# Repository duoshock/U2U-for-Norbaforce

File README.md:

#USB to USB for Norbaforce

This U2U is based on Hasu USB to USB with the rearranged component layout to fit Norbaforce housing. It's only compatible with Realforce R1 keyboard. However, It's easy to adapt it for Realforce R2 with the KiCad project.

QMK firmware is recommended - Enter DFU mode without having access to the physical rest switch with command keycode enable. (Although, there is a known issue of this port regarding not registering the board after computer reboot.)

Hasu U2U TMK firmware is also compatible.

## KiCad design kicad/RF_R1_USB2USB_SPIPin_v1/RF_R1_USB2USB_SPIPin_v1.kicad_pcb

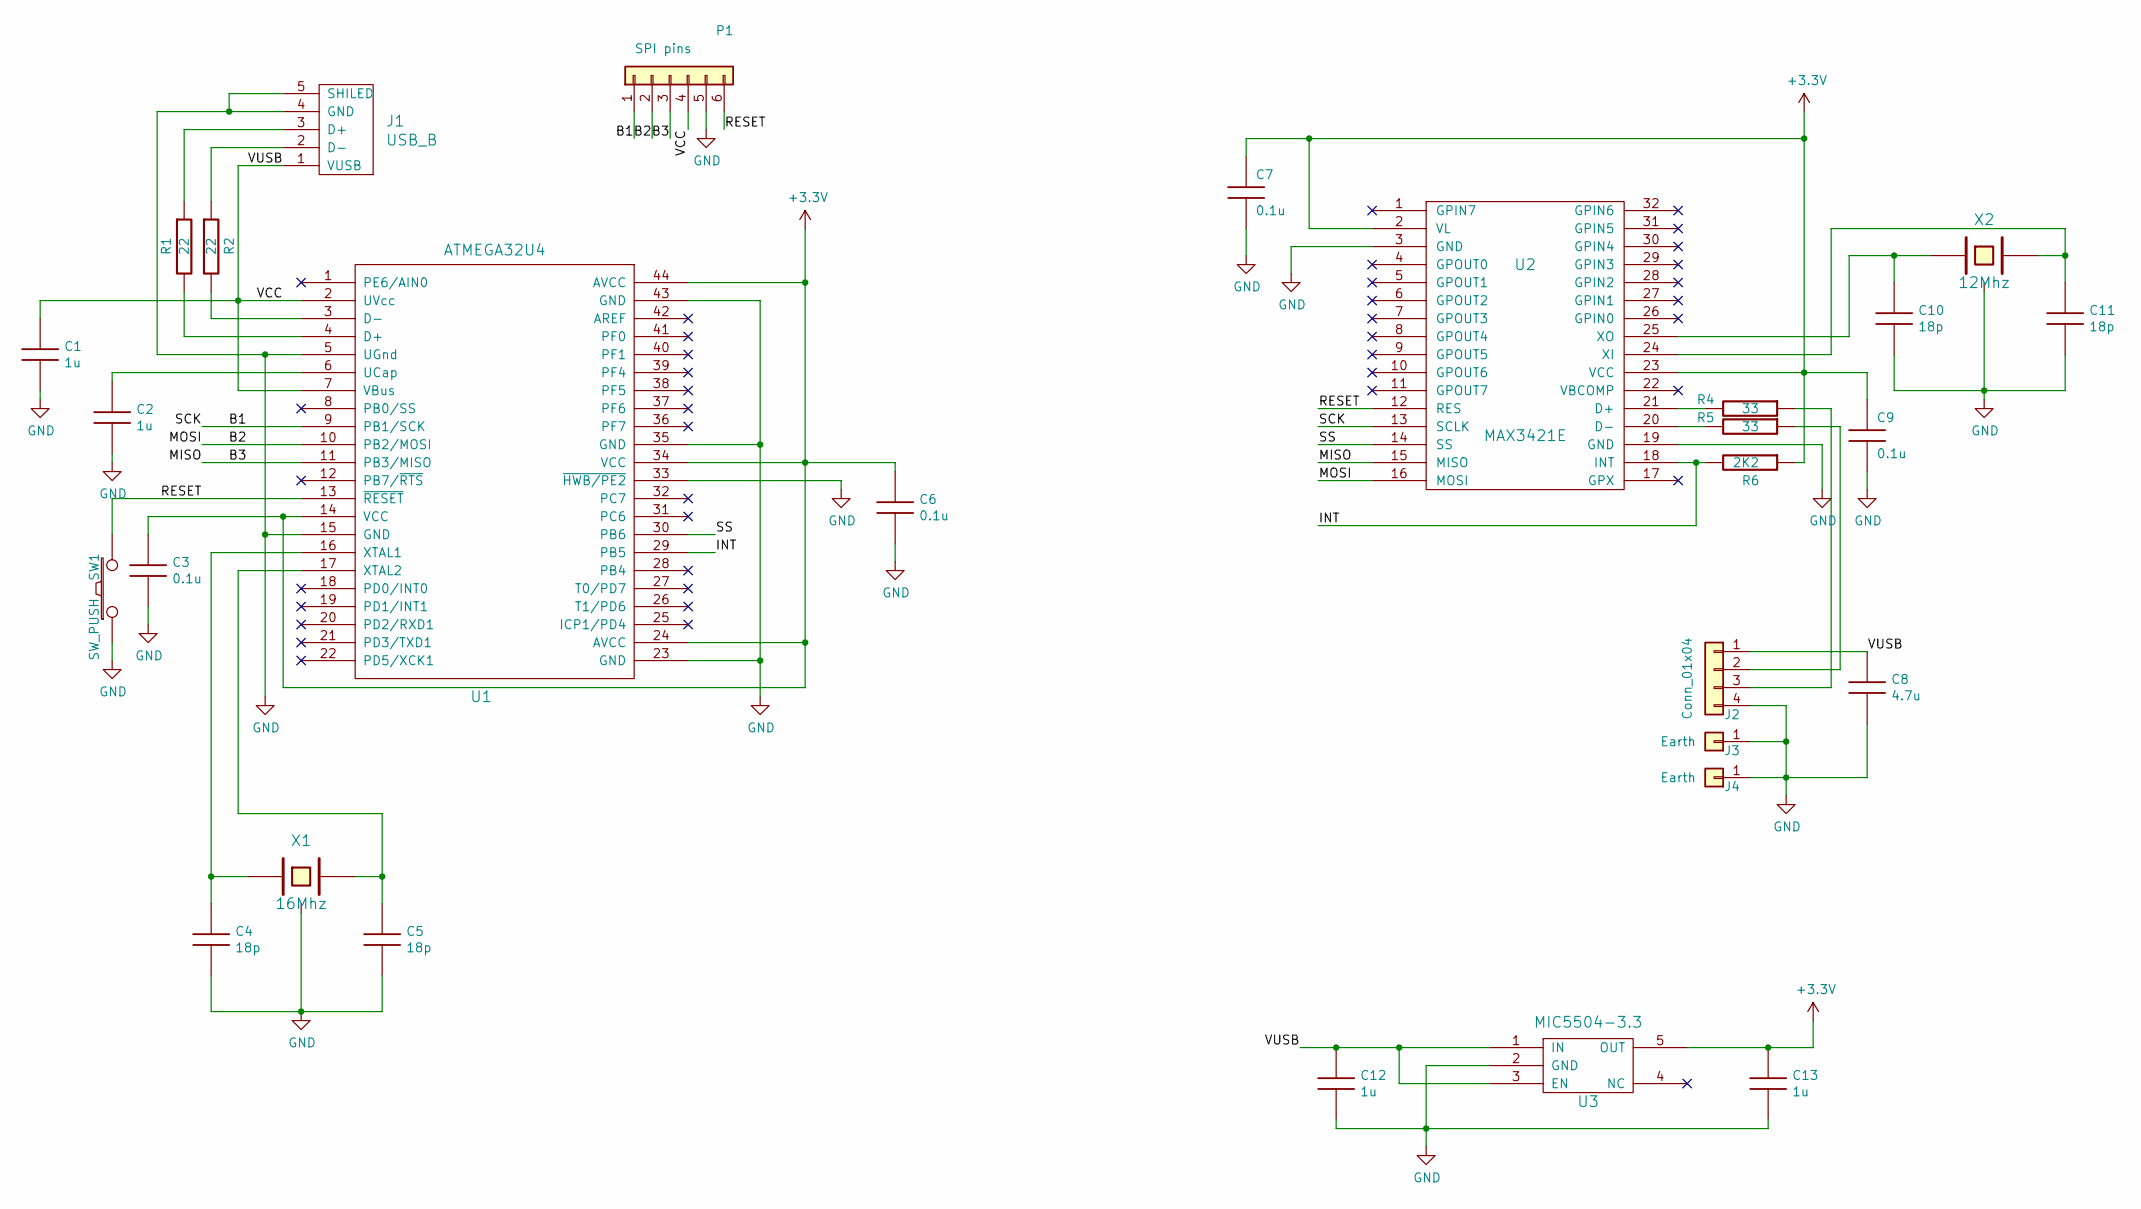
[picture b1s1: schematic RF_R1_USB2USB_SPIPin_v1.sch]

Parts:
C1, C2, C12, C13: 1u; C_0603
C3, C6, C7, C9: 0.1u; C_0603
C4, C5, C10, C11: 18p; C_0603
C8: 4.7u; C_0603
J1: USB_B; USB_Mini-B_Lumberg_2486_01_Horizontal
J2: Conn_01x04; JST_EH_S4B-EH_1x04_P2.50mm_Horizontal
J3, J4: Earth; MountingHole_3mm_Pad_Via
P1: SPI pins; Test Point 1mm x 6
R1, R2: 22; R_0603
R4, R5: 33; R_0603
R6: 2K2; R_0603
SW1: SW_PUSH; SW_SPST_B3U-1000P
U1: ATMEGA32U4; LQFP-44_10x10mm_P0.8mm
U2: MAX3421E; LQFP-32_5x5mm_P0.5mm
U3: MIC5504-3.3; SOT-23-5
X1: 16Mhz; Crystal_FA238-TSX3225
X2: 12Mhz; Crystal_FA238-TSX3225

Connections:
+3V3: C3.1, C6.1, C7.1, C9.1, C13.1, R6.1, U1.14 (VCC), U1.24 (AVCC), U1.34 (VCC), U1.44 (AVCC), U2.2 (VL), U2.23 (VCC), U3.5 (OUT)
/B1: P1.1, U1.9 (PB1/SCK), U2.13 (SCLK)
/B2: P1.2, U1.10 (PB2/MOSI), U2.16 (MOSI)
/B3: P1.3, U1.11 (PB3/MISO), U2.15 (MISO)
/INT: R6.2, U1.29 (PB5), U2.18 (INT)
/RESET: P1.6, SW1.2, U1.13 (~RESET), U2.12 (RES)
/SS: U1.30 (PB6), U2.14 (SS)
/VCC: C1.1, C8.1, C12.1, J1.1 (VUSB), J2.1, P1.4, U1.2 (UVcc), U1.7 (VBus), U3.1 (IN), U3.3 (EN)
GND: C1.2, C2.2, C3.2, C4.2, C5.2, C6.2, C7.2, C8.2, C9.2, C10.2, C11.2, C12.2, C13.2, J1.4 (GND), J1.5 (SHILED), J2.4, J3.1, J4.1, P1.5, SW1.1, U1.5 (UGnd), U1.15 (GND), U1.23 (GND), U1.33 (~HWB/PE2), U1.35 (GND), U1.43 (GND), U2.3 (GND), U2.19 (GND), U3.2 (GND), X1.3, X2.3
unnamed: C2.1, U1.6 (UCap)
unnamed: C4.1, U1.16 (XTAL1), X1.1
unnamed: C5.1, U1.17 (XTAL2), X1.2
unnamed: C10.1, U2.25 (XO), X2.1
unnamed: C11.1, U2.24 (XI), X2.2
unnamed: J1.2 (D-), R2.1
unnamed: J1.3 (D+), R1.1
unnamed: J2.2, R5.1
unnamed: J2.3, R4.1
unnamed: R1.2, U1.4 (D+)
unnamed: R2.2, U1.3 (D-)
unnamed: R4.2, U2.21 (D+)
unnamed: R5.2, U2.20 (D-)

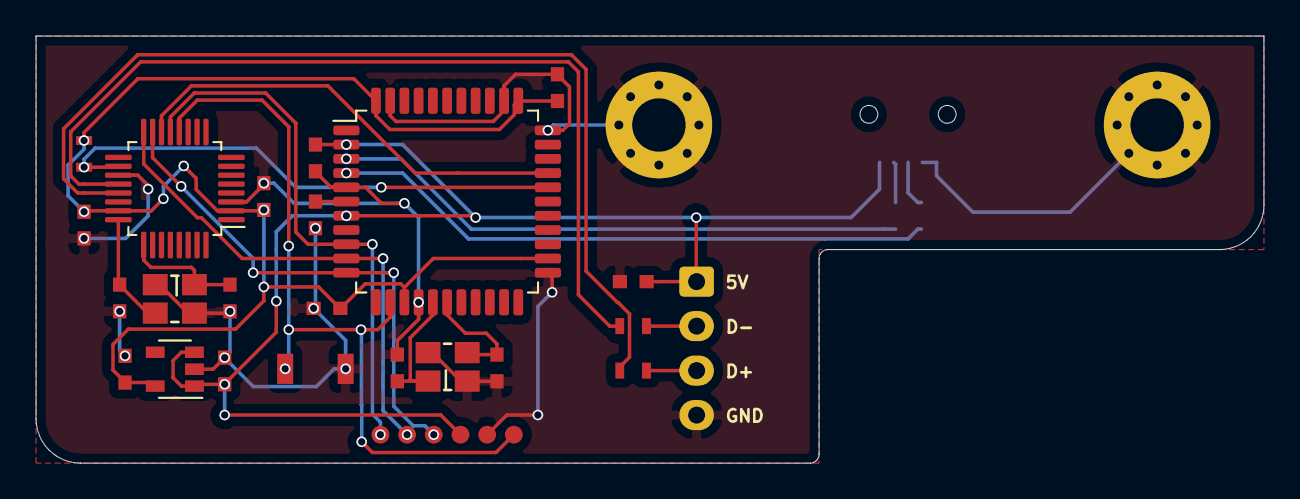
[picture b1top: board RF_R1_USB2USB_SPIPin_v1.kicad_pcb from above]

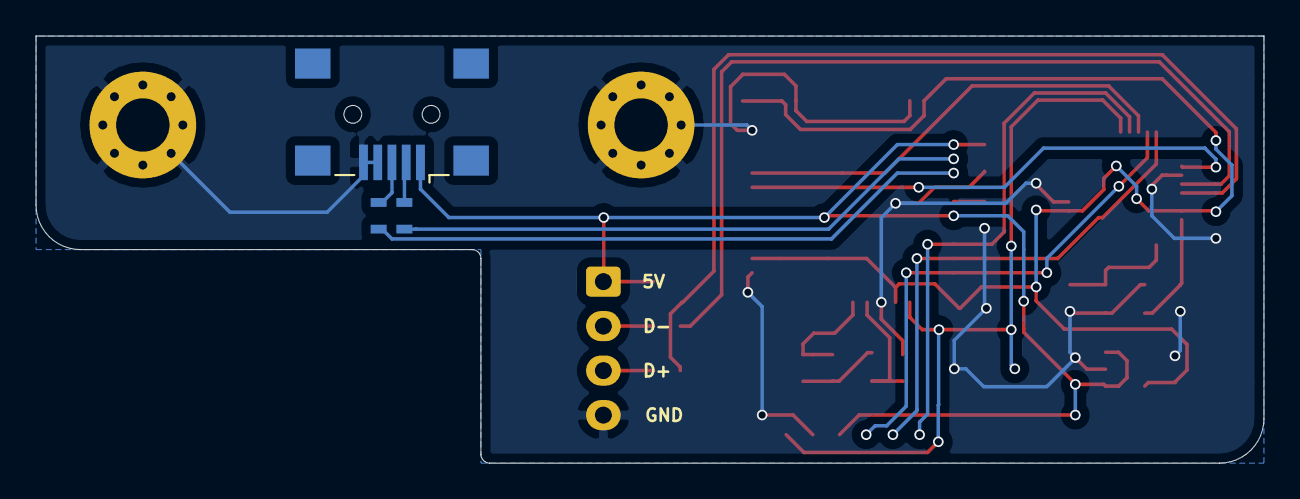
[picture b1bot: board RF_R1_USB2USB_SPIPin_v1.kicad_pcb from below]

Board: 2 copper layers, 69.0 x 24.0 mm, 29 parts (4 on the bottom side), 22 nets.

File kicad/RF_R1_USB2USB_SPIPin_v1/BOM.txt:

"Source:"	"M:\Miscellaneous\Keyboard\Realforce 91UDK-G\PCB\Project\RF_R1_USB2USB_SPIPin_v1\RF_R1_USB2USB_SPIPin_v1.sch"
"Date:"	"27/06/20 02:58:36"
"Tool:"	"Eeschema (5.1.4)-1"
"Component Count:"	"29"
"Ref"	"Value"	"Part"	"Footprint"	"Description"	"Vendor"
"C1"	"1u"	"keyboard_parts:C"	"Footprints:C_0603"	""	""
"C2"	"1u"	"keyboard_parts:C"	"Footprints:C_0603"	""	""
"C3"	"0.1u"	"keyboard_parts:C"	"Footprints:C_0603"	""	""
"C4"	"18p"	"keyboard_parts:C"	"Footprints:C_0603"	""	""
"C5"	"18p"	"keyboard_parts:C"	"Footprints:C_0603"	""	""
"C6"	"0.1u"	"keyboard_parts:C"	"Footprints:C_0603"	""	""
"C7"	"0.1u"	"keyboard_parts:C"	"Footprints:C_0603"	""	""
"C8"	"1u"	"keyboard_parts:C"	"Footprints:C_0603"	""	""
"C9"	"0.1u"	"keyboard_parts:C"	"Footprints:C_0603"	""	""
"C10"	"18p"	"keyboard_parts:C"	"Footprints:C_0603"	""	""
"C11"	"18p"	"keyboard_parts:C"	"Footprints:C_0603"	""	""
"C12"	"1u"	"keyboard_parts:C"	"Footprints:C_0603"	""	""
"C13"	"1u"	"keyboard_parts:C"	"Footprints:C_0603"	""	""
"J1"	"USB_B"	"keyboard_parts:USB_B"	"Connector_USB:USB_Mini-B_Lumberg_2486_01_Horizontal"	""	""
"J2"	"Conn_01x04"	"Connector_Generic:Conn_01x04"	"Connector_JST:JST_EH_S4B-EH_1x04_P2.50mm_Horizontal"	"Generic connector, single row, 01x04, script generated (kicad-library-utils/schlib/autogen/connector/)"	""
"J3"	"Earth"	"Connector_Generic:Conn_01x01"	"MountingHole:MountingHole_3mm_Pad_Via"	"Generic connector, single row, 01x01, script generated (kicad-library-utils/schlib/autogen/connector/)"	""
"J4"	"Earth"	"Connector_Generic:Conn_01x01"	"MountingHole:MountingHole_3mm_Pad_Via"	"Generic connector, single row, 01x01, script generated (kicad-library-utils/schlib/autogen/connector/)"	""
"P1"	"SPI pins"	"Connector_Generic:Conn_01x06"	"Footprints:Test Point 1mm x 6"	"Generic connector, single row, 01x06, script generated (kicad-library-utils/schlib/autogen/connector/)"	""
"R1"	"22"	"keyboard_parts:R"	"Footprints:R_0603"	""	""
"R2"	"22"	"keyboard_parts:R"	"Footprints:R_0603"	""	""
"R4"	"33"	"keyboard_parts:R"	"Footprints:R_0603"	""	""
"R5"	"33"	"keyboard_parts:R"	"Footprints:R_0603"	""	""
"R6"	"2K2"	"keyboard_parts:R"	"Footprints:R_0603"	""	""
"SW1"	"SW_PUSH"	"keyboard_parts:SW_PUSH"	"Footprints:SW_SPST_B3U-1000P"	""	""
"U1"	"ATMEGA32U4"	"keyboard_parts:ATMEGA32U4"	"Package_QFP:LQFP-44_10x10mm_P0.8mm"	""	""
"U2"	"MAX3421E"	"keyboard_parts:MAX3421E"	"Package_QFP:LQFP-32_5x5mm_P0.5mm"	""	""
"U3"	"MIC5504-3.3"	"keyboard_parts:LDO_REGULATOR"	"Package_TO_SOT_SMD:SOT-23-5"	"HOLTEK setup DC/DC converter"	""
"X1"	"16Mhz"	"keyboard_parts:XTAL_GND"	"Footprints:Crystal_FA238-TSX3225"	""	""
"X2"	"12Mhz"	"keyboard_parts:XTAL_GND"	"Footprints:Crystal_FA238-TSX3225"	""	""
